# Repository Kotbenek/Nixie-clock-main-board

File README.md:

# Moved to Codeberg

This repository was moved to Codeberg:
https://codeberg.org/Kotbenek/Nixie-clock-main-board

# Nixie-clock-main-board
Main PCB of my Nixie clock

## Board overview

- 12V AC input
- Rectified, smoothed 12V AC output (around 16V DC, powering the [180V power supply](https://github.com/Kotbenek/180V-power-supply))
- ATmega32 AVR microcontroller as the heart of the Nixie clock
- Photoresistor input for PWM Nixie tubes dimming
- Two inputs for external buttons used for timezone setting (UTC offset): TIMEZONE- and TIMEZONE+
- GPS module connector (3.3V, ground and GPS_TX line) with power on/off capability
- 6P6C connector used for interfacing the [Nixie clock tubes driver](https://github.com/Kotbenek/Nixie-clock-tubes-driver) board
- AVR ISP connector for AVR programming

## Images

## External 3D models used in the PCB render

- [Bridge rectifier](https://grabcad.com/library/bridge-rectifier-kbp-case-1)
- [Toroid inductor](https://grabcad.com/library/inductor-toroid-25mm-1)
- [6P6C connector](https://grabcad.com/library/rj12-1)

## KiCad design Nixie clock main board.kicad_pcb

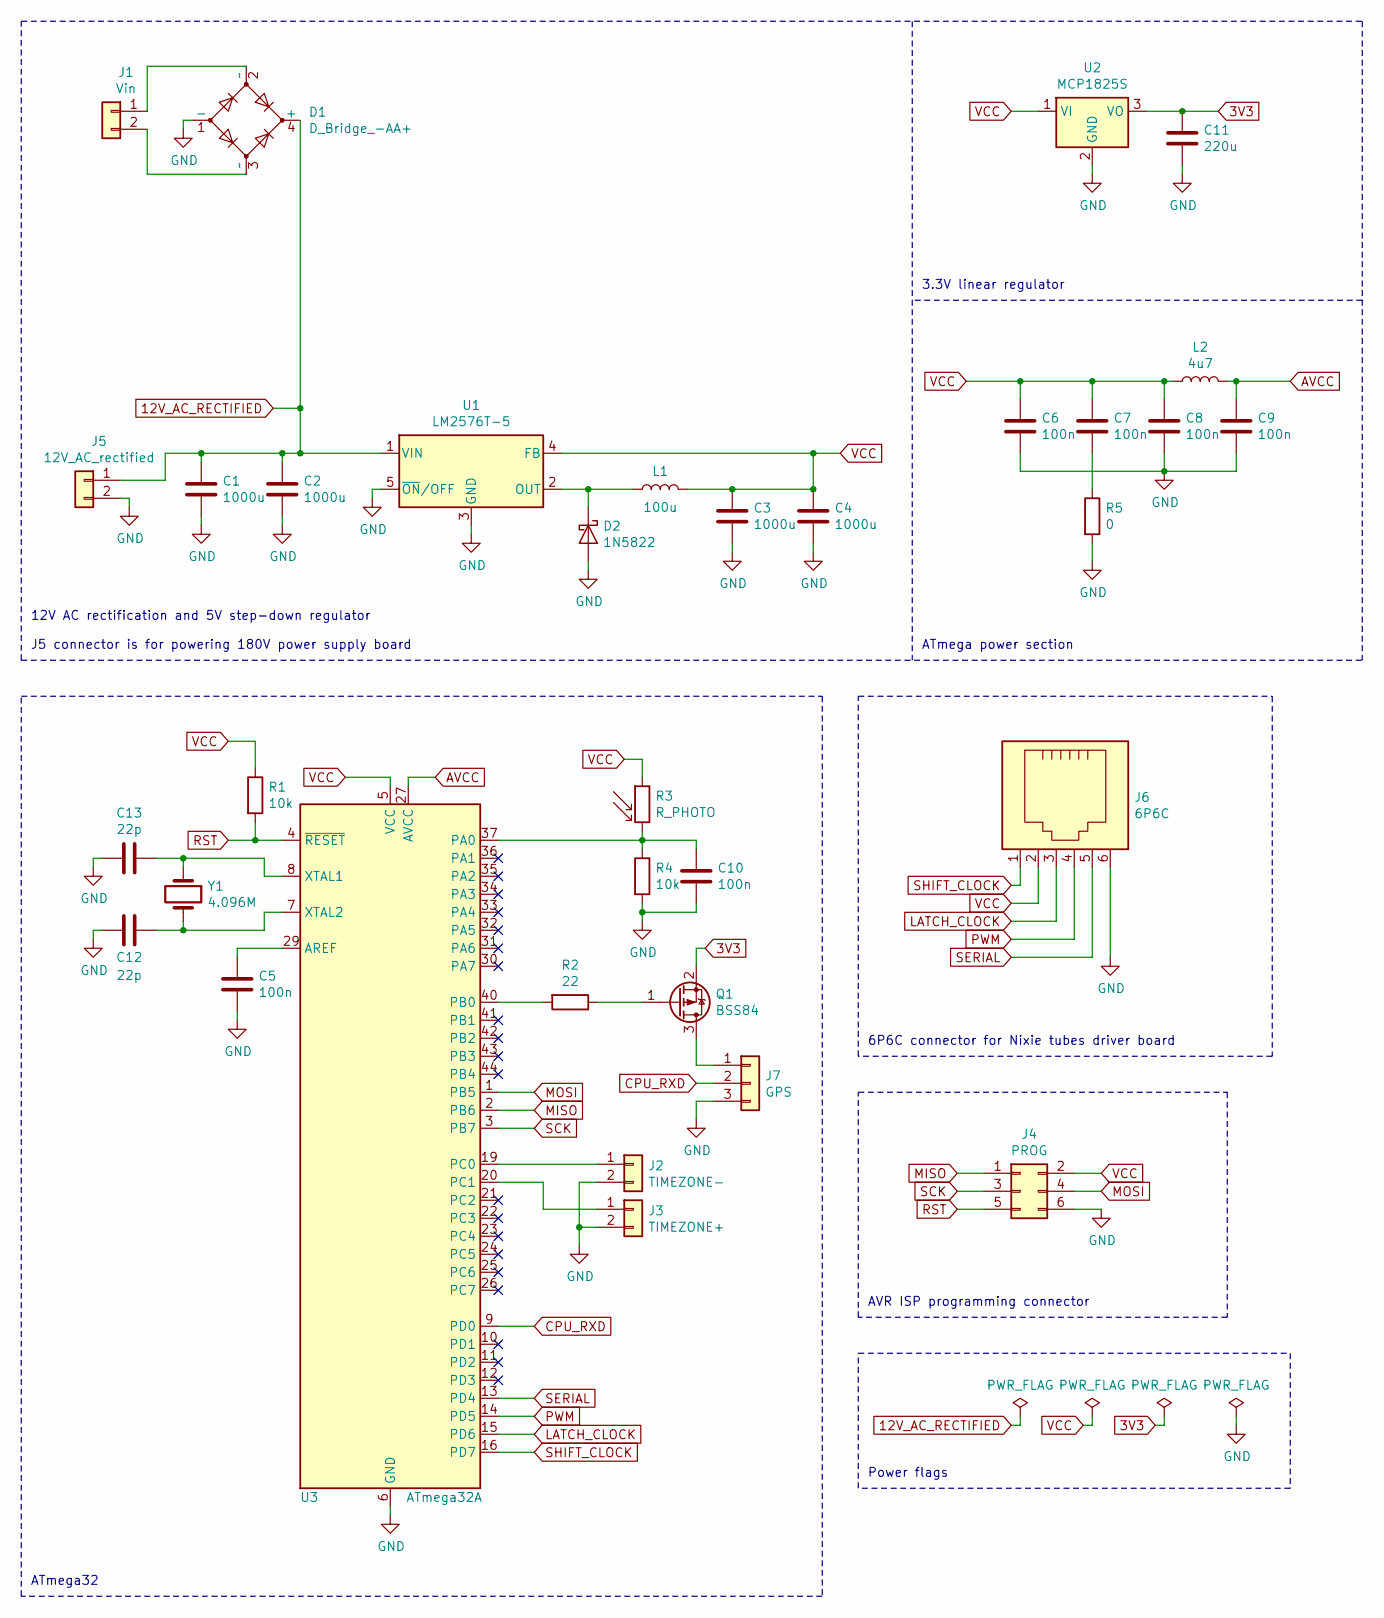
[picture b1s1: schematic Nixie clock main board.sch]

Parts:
C1, C2, C3, C4: 1000u; C_Radial_D10.0mm_H20.0mm_P5.00mm
C5, C6, C7, C8, C9, C10: 100n; C_0805_2012Metric
C11: 220u; CP_EIA-7132-28_AVX-C
C12, C13: 22p; C_0805_2012Metric
D1: D_Bridge_-AA+; TerminalBlock_bornier-4_P5.08mm
D2: 1N5822; D_DO-27_P15.24mm_Horizontal
J1: Vin; SolderWirePad_1x02_P3mm_10x5
J2: TIMEZONE-; PinHeader_1x02_P2.54mm_Vertical
J3: TIMEZONE+; PinHeader_1x02_P2.54mm_Vertical
J4: PROG; IDC-Header_2x03_P2.54mm_Vertical
J5: 12V_AC_rectified; SolderWirePad_1x02_P3mm_10x5
J6: 6P6C; RJ12_Amphenol_54601
J7: GPS; PinHeader_1x03_P2.54mm_Vertical
L1: 100u; L_Toroid_Vertical_L30mm_P13mm
L2: 4u7; L_0805_2012Metric
Q1: BSS84; SOT-23
R1, R4: 10k; R_0805_2012Metric
R2: 22; R_1206_3216Metric
R3: R_PHOTO; PinHeader_1x02_P2.54mm_Vertical
R5: 0; R_1206_3216Metric
U1: LM2576T-5; TO-220-5_Vertical
U2: MCP1825S; SOT-223-3_TabPin2
U3: ATmega32A; TQFP-44_10x10mm_P0.8mm
Y1: 4.096M; Crystal_HC49-U_Vertical

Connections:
3V3: C11.1, Q1.2 (S), U2.3 (VO)
12V_AC_RECTIFIED: C1.1, C2.1, D1.4 (+), J5.1, U1.1 (VIN)
AVCC: C9.1, L2.2, U3.27 (AVCC)
CPU_RXD: J7.2, U3.9 (PD0)
GND: C1.2, C2.2, C3.2, C4.2, C5.2, C6.2, C8.2, C9.2, C10.2, C11.2, C12.2, C13.2, D1.1 (-), D2.2 (A), J2.2, J3.2, J4.6, J5.2, J6.6, J7.3, R4.2, R5.2, U1.3 (GND), U1.5 (~ON~/OFF), U2.2 (GND), U3.6 (GND), U3.18 (GND), U3.28 (GND), U3.39 (GND)
LATCH_CLOCK: J6.3, U3.15 (PD6)
MISO: J4.1, U3.2 (PB6)
MOSI: J4.4, U3.1 (PB5)
unnamed: C5.1, U3.29 (AREF)
unnamed: C7.2, R5.1
unnamed: C10.1, R3.2, R4.1, U3.37 (PA0)
unnamed: C12.1, U3.7 (XTAL2), Y1.2
unnamed: C13.1, U3.8 (XTAL1), Y1.1
unnamed: D1.2 (~~), J1.1
unnamed: D1.3 (~~), J1.2
unnamed: D2.1 (K), L1.1, U1.2 (OUT)
unnamed: J2.1, U3.19 (PC0)
unnamed: J3.1, U3.20 (PC1)
unnamed: J7.1, Q1.3 (D)
unnamed: Q1.1 (G), R2.1
unnamed: R2.2, U3.40 (PB0)
PWM: J6.4, U3.14 (PD5)
RST: J4.5, R1.2, U3.4 (~RESET)
SCK: J4.3, U3.3 (PB7)
SERIAL: J6.5, U3.13 (PD4)
SHIFT_CLOCK: J6.1, U3.16 (PD7)
VCC: C3.1, C4.1, C6.1, C7.1, C8.1, J4.2, J6.2, L1.2, L2.1, R1.1, R3.1, U1.4 (FB), U2.1 (VI), U3.5 (VCC), U3.17 (VCC), U3.38 (VCC)

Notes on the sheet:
ATmega32
6P6C connector for Nixie tubes driver board
AVR ISP programming connector
Power flags
ATmega power section
3.3V linear regulator
12V AC rectification and 5V step-down regulator J5 connector is for powering 180V power supply board

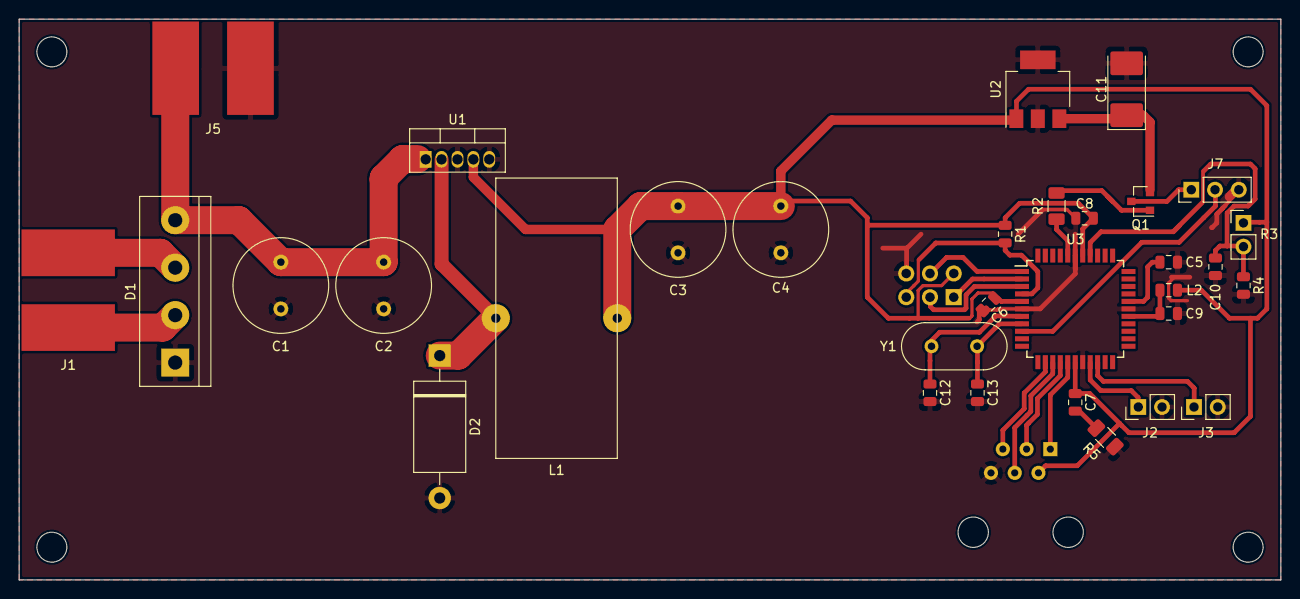
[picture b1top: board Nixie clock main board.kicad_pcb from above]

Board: 2 copper layers, 135.0 x 60.0 mm, 38 parts (0 on the bottom side), 27 nets.

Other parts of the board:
3mm hole, 3mm hole#2, 3mm hole#3, 3mm hole#4: MountingHole_3.2mm_M3_DIN965

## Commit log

2020-11-30 Version 1.0
2020-11-30 Added more PCB images
2020-11-30 Added gerber files
2020-11-30 Added schematic as pdf file
2020-11-30 Added mounting holes
2021-02-05 Updated README.md + minor fixes
2021-04-22 Added LICENSE.md
2021-09-03 Added missing gerber files
2024-09-25 LICENSE.md: Change line breaks from CRLF to LF
2024-09-25 LICENSE.md: Update date
2025-08-17 Moved to Codeberg
